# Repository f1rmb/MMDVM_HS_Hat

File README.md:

# MMDVM_HS_Hat
MMDVM_HS Hat for the Raspberry Pi (Zero)

This project provides a Raspberry Pi Hat for the [MMDVM_HS Hotspot](https://github.com/juribeparada/MMDVM_HS). It was designed for the Raspberry Pi Zero, but should work on any other Pi with the Hat interface. 

First revisions of the board have been built successfully!

The PCB is designed in KiCad and the necessary libraries are included. The supplied Gerber files can be used to order PCBs, for example at Elecrow or DirtyPCBs. The board's dimensions are 65x30mm.

__WARNING__
This fork was designed with KiCad 5 RC version (aka development build), opening the PCB file with KiCad 4 will simply fail.

You can order 3 beautiful, purple Revision 1.2 PCBs for $15 at [OSHPark](https://oshpark.com/shared_projects/WaiMw5XE)! 

## 3D printed Cases

Thanks to Toufik, F0DEI we added the ~~sources~~ STL files for a shiny case that you can print with your 3D printer. It may require a little upscaling depending on your printer model. It can carry a Raspberry Pi Zero (W) with MMDVM_HS_Hat (SMA) on top.

<br>
There are also the enclosures, designed by myself, available here https://github.com/f1rmb/MMDVM_HS_Hat-Enclosure

## Revisions
### Revision 0
This was the first released version that still contains a couple of errors. There is a trace missing between L1 and C1 that needs to be fixed with a small blob of solder or magnet wire. Otherwise the RF connector is not connected to the ADF7021. The GND side of C20 and C22 is not connected to the rest of the board's GND, this needs to be fixed with a little wire to any other GND. CE is connected directly to +3.3V which disallows mode scanning to work. If you just use one mode this is fine, otherwise the connection to the CE pin has to be cut and connected to PC14 on the STM32.

Earlier schematics showed C14 as 1uF. This is wrong and needs to be replaced with 1nF, otherwise the ADF7021 will neither receive nor transmit properly.

With these changes, you can build a fully working MMDVM_HS with the old revision 0 boards

### Revision 1
These boards have "Revision 1" written on them. All bugs found in revision 0 are fixed in this version. Apart from that, the STM32's BOOT0 and RESET pins are connected to GPIOs of the Raspberry Pi. This way, flashing should be possible without manually jumpering BOOT0 and triggering a reset.

Component placement did not change between revisions 0 and 1, therefore any stencils for revision 0 should work for revision 1 boards, too.

### Revision 1.1
Rewired 3v3 line for Nextion display connector to 5v0. Added SERVICE LED for visual heartbeat. Fixed improper labelling on P25 and YSF LEDs. Due to added LEDs this revision requires a new stencil.

### Revision 1.2
This Revision adds support for an optional AN1603-443 ceramic antenna. Insert C27 or C28, depending on what kind of antenna you want to use.

### Revision 1.3
The boot jumper was removed and the STlink header moved to its position. This gave space for another 4-pin header allowing to connect I²C OLED displays. No new stencil needed

### Revision 1.4
The SVC LED has been rotated and thus aligned to the layout of all other LEDs. The RainSun ceramic antenna has been replaced by a model that can be ordered at Mouser. DC line filtering has been added to 3v3 line.

### Revision 1.5
A fith mode LED has been added to the board to show NXDN activity. The two pin headers moved downwards a little. The rev1.4 stencil can be re-used if you manually add solder paste to R19 and D9 afterwards.

### Revision 1.6
Inner RX/TX pins of Nextion connector have been swapped. External VCO inductor L6 was added. This is optional for VHF use. D-Star and DMR LEDs were swapped to flash LEDs in proper scan order :).

### Revision 1.7
I will add the change list later, once the first PCB is assembled and tested :-D (PCB are on their way).

## BOM
* All necessary parts for the Revision 1.1 board can be ordered at Mouser using the following [shopping cart](http://www.mouser.com/ProjectManager/ProjectDetail.aspx?AccessID=780b8eac44)
* All necessary parts for the Revision 1.2 board can be ordered at Mouser using the following [shopping cart](http://www.mouser.com/ProjectManager/ProjectDetail.aspx?AccessID=035e777242)
* There is also a light version of revision 1.2 without the reset switch, 2.54mm headers and SMA connector [Link](http://www.mouser.com/ProjectManager/ProjectDetail.aspx?AccessID=3f7d0256e1)
* The parts for Revision 1.3 board are in this [Mouser cart](http://www.mouser.com/ProjectManager/ProjectDetail.aspx?AccessID=250d76339b) and the light version is [here](http://www.mouser.com/ProjectManager/ProjectDetail.aspx?AccessID=2d533ac53d)
* [Mouser project](http://www.mouser.com/ProjectManager/ProjectDetail.aspx?AccessID=5cab954f40) for MMDVM_HS_Hat revision 1.4
* There is another [Mouser cart for rev 1.5](https://www.mouser.com/ProjectManager/ProjectDetail.aspx?AccessID=5a3e4ae018).
* This is the [rev1.6 cart](https://www.mouser.com/ProjectManager/ProjectDetail.aspx?AccessID=48302f4221) and its [light version](https://www.mouser.com/ProjectManager/ProjectDetail.aspx?AccessID=ac888de33a).
* And this is the [Mouser cart for rev1.7](https://www.mouser.fr/ProjectManager/ProjectDetail.aspx?AccessID=95F1FF1BD5).

Please note that the onboard ceramic antenna is not supplied by Mouser and therefore missing in the carts for revisions up to 1.3.

Either the ADF7021 or the ADF7021-N can be used. Define the proper version in the firmware!

## Firmware Installation

### Compile and upload manually

For specific details about the firmware installation, check [these](https://github.com/juribeparada/MMDVM_HS#build-de-firmware-and-upload-to-zumspot-rpi) instructions. The process is similar to the installation on the ZumSpot Pi. 

Enable the following settings in Config.h:

    #define MMDVM_HS_HAT_REV12
    #define ENABLE_ADF7021
    #define ADF7021_14_7456
    #define STM32_USART1_HOST
    #define ENABLE_SCAN_MODE

Build the firmware:

    make

And finally upload the firmware to the MMDVM_HS_Hat:

    sudo make mmdvm_hs_hat

### Update within Pi-Star

Andy, MW0MWZ was so kind as to add a script which allows for updating the firmware of the MMDVM_HS_Hat within the running Pi-Star system. It uses the pre-compiled binaries from Andy's (CA6JAU) github repository. The update can be done with:

```
$ pistar-zumspotflash hs_hat
```

on the command line.

## Accessoires

* A case for the #MMDVM_HS_Hat can be found at amazon: [Case](https://www.amazon.de/Hochwertiges-schwarzes-auml-uuml-Raspberry/dp/B01FHDXNNU)

* An OLED display also to be found at amazon: [Display](https://www.amazon.de/dp/B01M9JVYIS/ref=cm_sw_r_wa_api_RmZ9zb01APZTV)

## License
This project is released under the Creative Commons Attribution-NonCommercial-ShareAlike 3.0 (CC-BY-NC-SA 3.0, https://creativecommons.org/licenses/by-nc-sa/3.0/) license. You may edit and share it as you like, as long as credit is given and the license is not changed. You can build as many boards for you and your friends as you like and you can even sell it to them to cover your costs, **however it is strictly forbidden to turn this into a commercial product! You are not allowed to build and sell these boards for profit!**

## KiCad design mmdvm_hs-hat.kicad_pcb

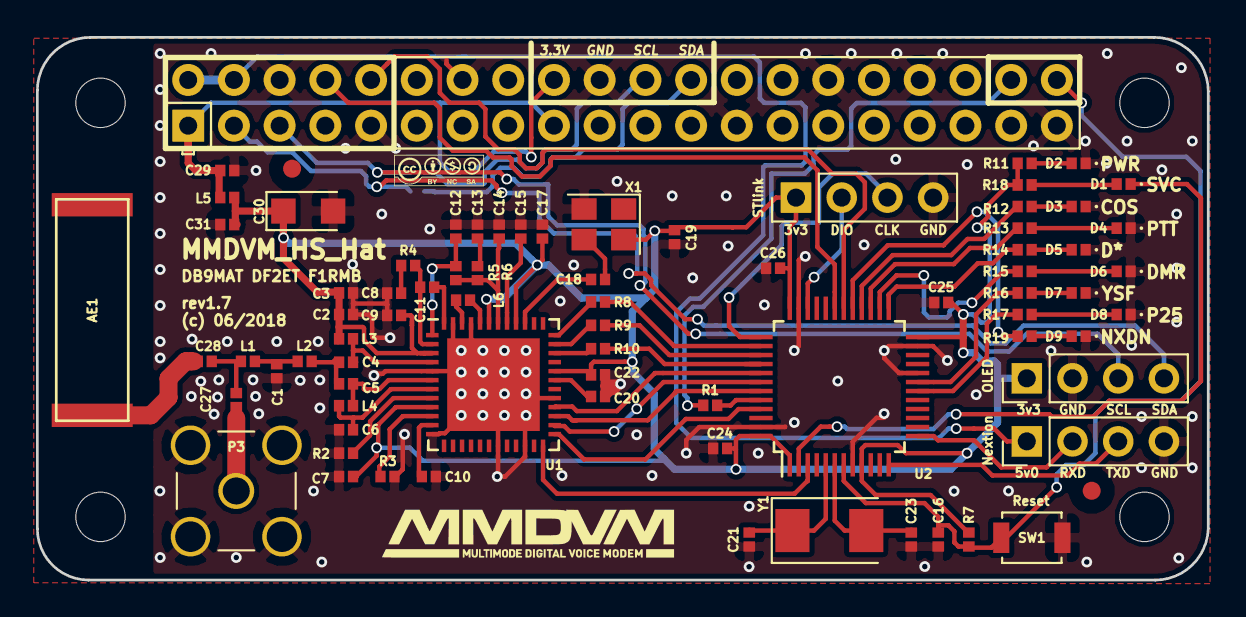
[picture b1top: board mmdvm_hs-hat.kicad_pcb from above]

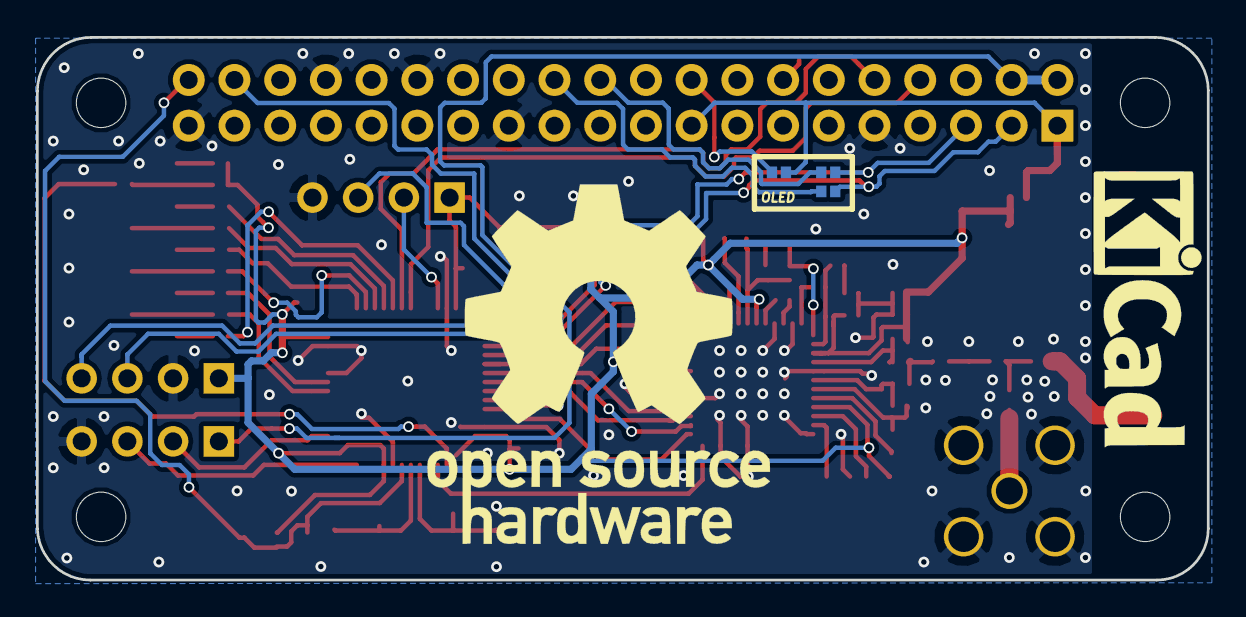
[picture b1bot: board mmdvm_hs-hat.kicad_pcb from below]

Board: 2 copper layers, 65.1 x 30.2 mm, 79 parts (3 on the bottom side), 71 nets.

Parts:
AE1: CERAMIC_ANTENNA; ANT1204
C1, C6: 6p8; C_0402_1005Metric
C2, C7, C9, C17, C19, C22: 10n; C_0402_1005Metric
C3: 220p; C_0402_1005Metric
C4: 10p; C_0402_1005Metric
C5: 4p7; C_0402_1005Metric
C8, C10, C15, C16, C20, C24, C25, C26, C27, C28, C29: 100n; C_0402_1005Metric
C11: 22n; C_0402_1005Metric
C12: 470p; C_0402_1005Metric
C13: 15n; C_0402_1005Metric
C14: 1n; C_0402_1005Metric
C18: 22p; C_0402_1005Metric
C21, C23: 20p; C_0402_1005Metric
C30: 10u/10V; CP_EIA-3216-18_Kemet-A
C31: 10u; C_0402_1005Metric
D1, D4, D8: red; LED_0402_1005Metric
D2, D5: green; LED_0402_1005Metric
D3, D6: yellow; LED_0402_1005Metric
D7: amber; LED_0402_1005Metric
D9: blue; LED_0402_1005Metric
L1: 22n; L_0402_1005Metric
L2: 20n; L_0402_1005Metric
L3: 13n; L_0402_1005Metric
L4: 27n; L_0402_1005Metric
L5: 10u; L_0402_1005Metric
L6: 18n; L_0402_1005Metric
P1: I2C; PinHeader_1x04_P2.54mm_Vertical
P2: DISPLAY; PinHeader_1x04_P2.54mm_Vertical
P3: SMA; SMA_THT_Jack_Straight
P4: STLINK; PinHeader_1x04_P2.54mm_Vertical
PI1: RPI-ZERO; RPI-Zero-RASPBERRYPI_BASTELSTUBE_V13_RASPI_BOARD_B+_FULL
R1, R7: 10k; R_0402_1005Metric
R2: 1k1; R_0402_1005Metric
R3: 3k8; R_0402_1005Metric
R4: 3r9; R_0402_1005Metric
R5: 560; R_0402_1005Metric
R6: 270; R_0402_1005Metric
R8, R9, R10, R11, R12, R13, R14, R15, R16, R17, R18, R19: 1k; R_0402_1005Metric
R20, R21, R22: DNI; R_0402_1005Metric
SW1: DNI; SW_SPST_B3U-1000P
U1: ADF7021; QFN-48-1EP_7x7mm_Pitch0.5mm
U2: STM32F103C8T6; LQFP-48_7x7mm_Pitch0.5mm
X1: TCXO; Crystal_SMD_3225-4pin_3.2x2.5mm
Y1: 8MHz; Crystal_SMD_Abracon_ABM3-2pin_5.0x3.2mm

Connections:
+3V3: C29.1, L5.1, PI1.1, PI1.17, R20.1
+5V: P2.1, PI1.2, PI1.4
BOOT0: R1.1, U2.44
CE: U1.24, U2.3
CLKOUT: R8.1, U2.38
COS_LED: R12.2, U2.28
DATAIN: R9.1, U2.39
DATAOUT: R10.1, U2.40
DISP_RXD: P2.2, U2.13
DISP_TXD: P2.3, U2.12
DMR_LED: R15.2, U2.26
DSTAR_LED: R14.2, U2.25
GND: C1.2, C2.2, C3.2, C6.2, C7.2, C8.2, C9.2, C10.2, C12.2, C13.2, C14.2, C15.1, C16.2, C17.2, C19.2, C20.1, C21.1, C22.1, C23.1, C24.2, C25.2, C26.2, C29.2, C30.2, C31.2, D2.1, D3.1, D4.1, D5.1, D6.1, D7.1, D8.1, D9.1, P1.2, P2.4, P3.2, P4.4, PI1.6, PI1.9, PI1.14, PI1.20, PI1.25, PI1.30, PI1.34, PI1.39, R2.2, R3.2, SW1.2, U1.5, U1.12, U1.19, U1.22, U1.29, U1.45, U1.47, U1.49, U2.8, U2.20, U2.23, U2.35, U2.47, X1.2
NRST: C16.1, PI1.40, R7.1, SW1.1, U2.7
NXDN_LED: R19.2, U2.29
unnamed: AE1.1, C28.2
unnamed: C1.1, L1.2, L2.1
unnamed: C4.1, L3.1, U1.4
unnamed: C4.2, C5.2, L2.2
unnamed: C5.1, L4.2, U1.6
unnamed: C6.1, L4.1, U1.7
unnamed: C8.1, R4.2
unnamed: C10.1, U1.11
unnamed: C11.1, U1.48
unnamed: C11.2, R4.1, U1.2
unnamed: C12.1, R5.2, U1.1
unnamed: C13.1, R6.2
unnamed: C14.1, R5.1, R6.1, U1.42
unnamed: C15.2, U1.41
unnamed: C18.1, X1.3
unnamed: C18.2, U1.39
unnamed: C20.2, U1.31
unnamed: C21.2, U2.5, Y1.1
unnamed: C23.2, U2.6, Y1.2
unnamed: C27.1, P3.1
unnamed: D1.2, R18.2
unnamed: D2.2, R11.1
unnamed: D3.2, R12.1
unnamed: D4.2, R13.1
unnamed: D5.2, R14.1
unnamed: D6.2, R15.1
unnamed: D7.2, R16.1
unnamed: D8.2, R17.1
unnamed: D9.2, R19.1
unnamed: L6.1, U1.46
unnamed: L6.2, U1.44
unnamed: PI1.18, R20.2
unnamed: PI1.22, R21.2
unnamed: PI1.24, R22.2
unnamed: PI1.38, R1.2
unnamed: R2.1, U1.8
unnamed: R3.1, U1.10
unnamed: R8.2, U1.36
unnamed: R9.2, U1.35
unnamed: R10.2, U1.34
P25_LED: R17.2, U2.18
PTT_LED: R13.2, U2.27
RF: C27.2, C28.1, L1.1
RXD: PI1.8, U2.31
SCL: P1.3, PI1.5, R21.1
SCLK: U1.28, U2.41
SDA: P1.4, PI1.3, R22.1
SDATA: U1.26, U2.42
SERVICE: D1.1, U2.2
SLE: U1.25, U2.45
SREAD: U1.27, U2.43
SWCLK: P4.3, U2.37
SWDIO: P4.2, U2.34
TXD: PI1.10, U2.30
VDD: C2.1, C3.1, C7.1, C9.1, C17.1, C19.1, C22.2, C24.1, C25.1, C26.1, C30.1, C31.1, L3.2, L5.2, P1.1, P4.1, R7.2, R11.2, R18.1, U1.3, U1.9, U1.32, U1.40, U1.43, U2.1, U2.9, U2.24, U2.36, U2.48, X1.4
YSF_LED: R16.2, U2.19

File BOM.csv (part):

Source:,/home/caudanie/Documents/KiCadProjects/MMDVM_HS_Hat/mmdvm_hs-hat.sch,,,,,,,,,,
Date:,Mon 28 May 2018 01:47:52 PM CEST,,,,,,,,,,
Tool:,Eeschema 5.0.0-rc2-unknown-da66005~65~ubuntu16.04.1,,,,,,,,,,
Generator:,/usr/lib/x86_64-linux-gnu/kicad/plugins/bom_csv_grouped_by_value.py,,,,,,,,,,
Component Count:,76,,,,,,,,,,
,,,,,,,,,,,
Individual Components:,,,,,,,,,,,
,,,,,,,,,,,
Item,Qty,Reference(s),Value,LibPart,Footprint,Datasheet,MFR,MPN,SPN,SPR,SPURL
,,AE1,CERAMIC_ANTENNA,mmdvm_hs-hat-rescue:Antenna_Dipole-RESCUE-mmdvm_hs-hat,MMDVM:ANT1204,http://www.mouser.com/ds/2/447/An_SMD_UHF_433_1204_0-595178.pdf,Yageo,ANT1204F002R0433A,603-ANT1204F002R0433,Mouser,
,,C1,6p8,mmdvm_hs-hat-rescue:C-RESCUE-mmdvm_hs-hat,Capacitor_SMD:C_0402_1005Metric,http://www.mouser.com/ds/2/281/c02e-2905.pdf,Murata Electronics,GJM1555C1H6R8BB01D,81-GJM1555C1H6R8BB1D,Mouser,
,,C2,10n,mmdvm_hs-hat-rescue:C-RESCUE-mmdvm_hs-hat,Capacitor_SMD:C_0402_1005Metric,http://www.mouser.com/ds/2/427/vjw1bcbascomseries-223529.pdf,Vishay / Vitramon,VJ0402Y103KXJCW1BC,77-VJ0402Y103KXJCBC,Mouser,
,,C3,220p,mmdvm_hs-hat-rescue:C-RESCUE-mmdvm_hs-hat,Capacitor_SMD:C_0402_1005Metric,http://www.mouser.com/ds/2/281/c02e-2905.pdf,Murata Electronics,GRM1555C1H221JA01D,81-GRM1555C1H221JA01,Mouser,
,,C4,10p,mmdvm_hs-hat-rescue:C-RESCUE-mmdvm_hs-hat,Capacitor_SMD:C_0402_1005Metric,http://www.mouser.com/ds/2/281/c02e-2905.pdf,Murata Electronics,GRM1555C1E100GA01D,81-GRM1555C1E100GA1D,Mouser,
,,C5,4p7,mmdvm_hs-hat-rescue:C-RESCUE-mmdvm_hs-hat,Capacitor_SMD:C_0402_1005Metric,http://www.mouser.com/ds/2/281/c02e-2905.pdf,Murata Electronics,GRM1555C1H4R7CA01D,81-GRM1555C1H4R7CA1D,Mouser,
,,C6,6p8,mmdvm_hs-hat-rescue:C-RESCUE-mmdvm_hs-hat,Capacitor_SMD:C_0402_1005Metric,http://www.mouser.com/ds/2/281/c02e-2905.pdf,Murata Electronics,GJM1555C1H6R8BB01D,81-GJM1555C1H6R8BB1D,Mouser,
,,C7,10n,mmdvm_hs-hat-rescue:C-RESCUE-mmdvm_hs-hat,Capacitor_SMD:C_0402_1005Metric,http://www.mouser.com/ds/2/427/vjw1bcbascomseries-223529.pdf,Vishay / Vitramon,VJ0402Y103KXJCW1BC,77-VJ0402Y103KXJCBC,Mouser,
,,C8,100n,mmdvm_hs-hat-rescue:C-RESCUE-mmdvm_hs-hat,Capacitor_SMD:C_0402_1005Metric,http://www.mouser.com/ds/2/427/vjw1bcbascomseries-223529.pdf,Vishay / Vitramon,VJ0402V104ZXJCW1BC,77-VJ0402V104ZXJCBC,Mouser,
,,C9,10n,mmdvm_hs-hat-rescue:C-RESCUE-mmdvm_hs-hat,Capacitor_SMD:C_0402_1005Metric,http://www.mouser.com/ds/2/427/vjw1bcbascomseries-223529.pdf,Vishay / Vitramon,VJ0402Y103KXJCW1BC,77-VJ0402Y103KXJCBC,Mouser,
,,C10,100n,mmdvm_hs-hat-rescue:C-RESCUE-mmdvm_hs-hat,Capacitor_SMD:C_0402_1005Metric,http://www.mouser.com/ds/2/427/vjw1bcbascomseries-223529.pdf,Vishay / Vitramon,VJ0402V104ZXJCW1BC,77-VJ0402V104ZXJCBC,Mouser,
,,C11,22n,mmdvm_hs-hat-rescue:C-RESCUE-mmdvm_hs-hat,Capacitor_SMD:C_0402_1005Metric,http://www.mouser.com/ds/2/281/c03e-806517.pdf,Murata Electronics,GCM155R71E223KA55D,81-GCM155R71E223KA5D,Mouser,
,,C12,470p,mmdvm_hs-hat-rescue:C-RESCUE-mmdvm_hs-hat,Capacitor_SMD:C_0402_1005Metric,http://www.mouser.com/ds/2/281/c02e-2905.pdf,Murata Electronics,GRM155R71H471KA01D,81-GRM36X471K50,Mouser,
,,C13,15n,mmdvm_hs-hat-rescue:C-RESCUE-mmdvm_hs-hat,Capacitor_SMD:C_0402_1005Metric,http://www.mouser.com/ds/2/281/c02e-2905.pdf,Murata Electronics,GRM155R71C153KA01D,81-GRM155R71C153KA1D,Mouser,
,,C14,1n,mmdvm_hs-hat-rescue:C-RESCUE-mmdvm_hs-hat,Capacitor_SMD:C_0402_1005Metric,http://www.mouser.com/ds/2/281/c02e-2905.pdf,Murata Electronics,GRM155R60J102KA01D,81-GRM155R60J102KA1D,Mouser,
,,C15,100n,mmdvm_hs-hat-rescue:C-RESCUE-mmdvm_hs-hat,Capacitor_SMD:C_0402_1005Metric,http://www.mouser.com/ds/2/427/vjw1bcbascomseries-223529.pdf,Vishay / Vitramon,VJ0402V104ZXJCW1BC,77-VJ0402V104ZXJCBC,Mouser,
,,C16,100n,mmdvm_hs-hat-rescue:C-RESCUE-mmdvm_hs-hat,Capacitor_SMD:C_0402_1005Metric,http://www.mouser.com/ds/2/427/vjw1bcbascomseries-223529.pdf,Vishay / Vitramon,VJ0402V104ZXJCW1BC,77-VJ0402V104ZXJCBC,Mouser,
,,C17,10n,mmdvm_hs-hat-rescue:C-RESCUE-mmdvm_hs-hat,Capacitor_SMD:C_0402_1005Metric,http://www.mouser.com/ds/2/427/vjw1bcbascomseries-223529.pdf,Vishay / Vitramon,VJ0402Y103KXJCW1BC,77-VJ0402Y103KXJCBC,Mouser,
,,C18,22p,mmdvm_hs-hat-rescue:C-RESCUE-mmdvm_hs-hat,Capacitor_SMD:C_0402_1005Metric,http://www.mouser.com/ds/2/40/C0GNP0-Dielectric-951274.pdf,AVX,04025A220GAT2A,581-04025A220G,Mouser,
,,C19,10n,mmdvm_hs-hat-rescue:C-RESCUE-mmdvm_hs-hat,Capacitor_SMD:C_0402_1005Metric,http://www.mouser.com/ds/2/427/vjw1bcbascomseries-223529.pdf,Vishay / Vitramon,VJ0402Y103KXJCW1BC,77-VJ0402Y103KXJCBC,Mouser,
,,C20,100n,mmdvm_hs-hat-rescue:C-RESCUE-mmdvm_hs-hat,Capacitor_SMD:C_0402_1005Metric,http://www.mouser.com/ds/2/427/vjw1bcbascomseries-223529.pdf,Vishay / Vitramon,VJ0402V104ZXJCW1BC,77-VJ0402V104ZXJCBC,Mouser,
,,C21,20p,mmdvm_hs-hat-rescue:C-RESCUE-mmdvm_hs-hat,Capacitor_SMD:C_0402_1005Metric,http://www.mouser.com/ds/2/281/c02e-2905.pdf,Murata Electronics,GJM1555C1H200FB01D,81-GJM1555C1H200FB1D,Mouser,
,,C22,10n,mmdvm_hs-hat-rescue:C-RESCUE-mmdvm_hs-hat,Capacitor_SMD:C_0402_1005Metric,http://www.mouser.com/ds/2/427/vjw1bcbascomseries-223529.pdf,Vishay / Vitramon,VJ0402Y103KXJCW1BC,77-VJ0402Y103KXJCBC,Mouser,
,,C23,20p,mmdvm_hs-hat-rescue:C-RESCUE-mmdvm_hs-hat,Capacitor_SMD:C_0402_1005Metric,http://www.mouser.com/ds/2/281/c02e-2905.pdf,Murata Electronics,GJM1555C1H200FB01D,81-GJM1555C1H200FB1D,Mouser,
,,C24,100n,mmdvm_hs-hat-rescue:C-RESCUE-mmdvm_hs-hat,Capacitor_SMD:C_0402_1005Metric,http://www.mouser.com/ds/2/427/vjw1bcbascomseries-223529.pdf,Vishay / Vitramon,VJ0402V104ZXJCW1BC,77-VJ0402V104ZXJCBC,Mouser,
,,C25,100n,mmdvm_hs-hat-rescue:C-RESCUE-mmdvm_hs-hat,Capacitor_SMD:C_0402_1005Metric,http://www.mouser.com/ds/2/427/vjw1bcbascomseries-223529.pdf,Vishay / Vitramon,VJ0402V104ZXJCW1BC,77-VJ0402V104ZXJCBC,Mouser,
,,C26,100n,mmdvm_hs-hat-rescue:C-RESCUE-mmdvm_hs-hat,Capacitor_SMD:C_0402_1005Metric,http://www.mouser.com/ds/2/427/vjw1bcbascomseries-223529.pdf,Vishay / Vitramon,VJ0402V104ZXJCW1BC,77-VJ0402V104ZXJCBC,Mouser,
,,C27,100n,mmdvm_hs-hat-rescue:C-RESCUE-mmdvm_hs-hat,Capacitor_SMD:C_0402_1005Metric,http://www.mouser.com/ds/2/427/vjw1bcbascomseries-223529.pdf,Vishay / Vitramon,VJ0402V104ZXJCW1BC,77-VJ0402V104ZXJCBC,Mouser,
,,C28,100n,mmdvm_hs-hat-rescue:C-RESCUE-mmdvm_hs-hat,Capacitor_SMD:C_0402_1005Metric,http://www.mouser.com/ds/2/427/vjw1bcbascomseries-223529.pdf,Vishay / Vitramon,VJ0402V104ZXJCW1BC,77-VJ0402V104ZXJCBC,Mouser,
,,C29,100n,mmdvm_hs-hat-rescue:C-RESCUE-mmdvm_hs-hat,Capacitor_SMD:C_0402_1005Metric,http://www.mouser.com/ds/2/427/vjw1bcbascomseries-223529.pdf,Vishay / Vitramon,VJ0402V104ZXJCW1BC,77-VJ0402V104ZXJCBC,Mouser,
,,C30,10u/10V,mmdvm_hs-hat-rescue:CP-RESCUE-mmdvm_hs-hat,Capacitor_Tantalum_SMD:CP_EIA-3216-18_Kemet-A,http://www.mouser.com/ds/2/40/f93-776559.pdf,AVX,F931A106KAA,647-F931A106KAA,Mouser,
,,C31,10u,mmdvm_hs-hat-rescue:C-RESCUE-mmdvm_hs-hat,Capacitor_SMD:C_0402_1005Metric,http://www.mouser.com/ds/2/281/c02e-2905.pdf,Murata Electronics,GRJ155R60J106ME11D,81-GRJ155R60J106ME1D,Mouser,
,,D1,red,mmdvm_hs-hat-rescue:LED-RESCUE-mmdvm_hs-hat,LED_SMD:LED_0402_1005Metric,http://www.mouser.com/ds/2/216/APHHS1005SURCK-32322.pdf,Kingbright,APHHS1005SURCK,604-APHHS1005SURCK,Mouser,
,,D2,green,mmdvm_hs-hat-rescue:LED-RESCUE-mmdvm_hs-hat,LED_SMD:LED_0402_1005Metric,http://www.mouser.com/ds/2/216/APHHS1005CGCK-38896.pdf,Kingbright,APHHS1005CGCK,604-APHHS1005CGCK,Mouser,
,,D3,yellow,mmdvm_hs-hat-rescue:LED-RESCUE-mmdvm_hs-hat,LED_SMD:LED_0402_1005Metric,http://www.mouser.com/ds/2/216/APG1005SYC-T-315808.pdf,Kingbright,APG1005SYC-T,604-APG1005SYCT,Mouser,
,,D4,red,mmdvm_hs-hat-rescue:LED-RESCUE-mmdvm_hs-hat,LED_SMD:LED_0402_1005Metric,http://www.mouser.com/ds/2/216/APHHS1005SURCK-32322.pdf,Kingbright,APHHS1005SURCK,604-APHHS1005SURCK,Mouser,
,,D5,green,mmdvm_hs-hat-rescue:LED-RESCUE-mmdvm_hs-hat,LED_SMD:LED_0402_1005Metric,http://www.mouser.com/ds/2/216/APG1005SYC-T-315808.pdf,Kingbright,APG1005SYC-T,604-APG1005SYCT,Mouser,
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
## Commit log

2018-05-16 Fix ERC warnings, update pin directions on devices.
2018-05-16 Rotate 180° STLink connector (respect OLED and Nextion orientations). Replace GND pads to VIA (netlist can be safely updated from schematic now). Reroute Service track. Small tweaks to various tracks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
2018-05-16 Packages has been updated to latest KiCAD (daily) naming scheme, with few execptions. Rotate 180° STLink connector (respect OLED and Nextion orientations). Replace GND pads to VIA (netlist can be saf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
2018-05-16 Update 3D image location (temporary).
2018-05-17 Add ceramic antenna and LED 3d step files.
2018-05-17 A bit of reorg. 3D shapes in their own packages3d/subdir.
2018-05-17 Update 3D picture.
2018-05-17 Few track re-routed, few components moved. SMA sligthly moved to get better GND one for corners. Center tracks in 2x20 connector.
2018-05-18 Add a wearning about KiCAD 5.
2018-05-18 KiCAD -> KiCad.
2018-05-28 Small changes with package for this board rev (needed to modelize the enclosure).
2018-05-28 Update the BOM.
2018-05-29 Add I2C OLED on 2x20 connector (should make it optional).
2018-05-30 Make OLED_on_2x20 optionnal, electrically (using 3x0402 unpopulated resistors).
2018-05-30 Fine tunning some tracks.
2018-06-06 Fix DRC's fiducial warning.
2018-06-08 Updated Gerber files for r1.7.
2018-06-08 Last silkscreen changes for this release.
2018-06-08 Update picture.
2018-06-16 Update enclosures informations in the README, mention my enclosures.
2018-06-16 Typo.
2018-06-16 Mention 1.7 version.
2018-06-21 Add cart link for rev1.7.
